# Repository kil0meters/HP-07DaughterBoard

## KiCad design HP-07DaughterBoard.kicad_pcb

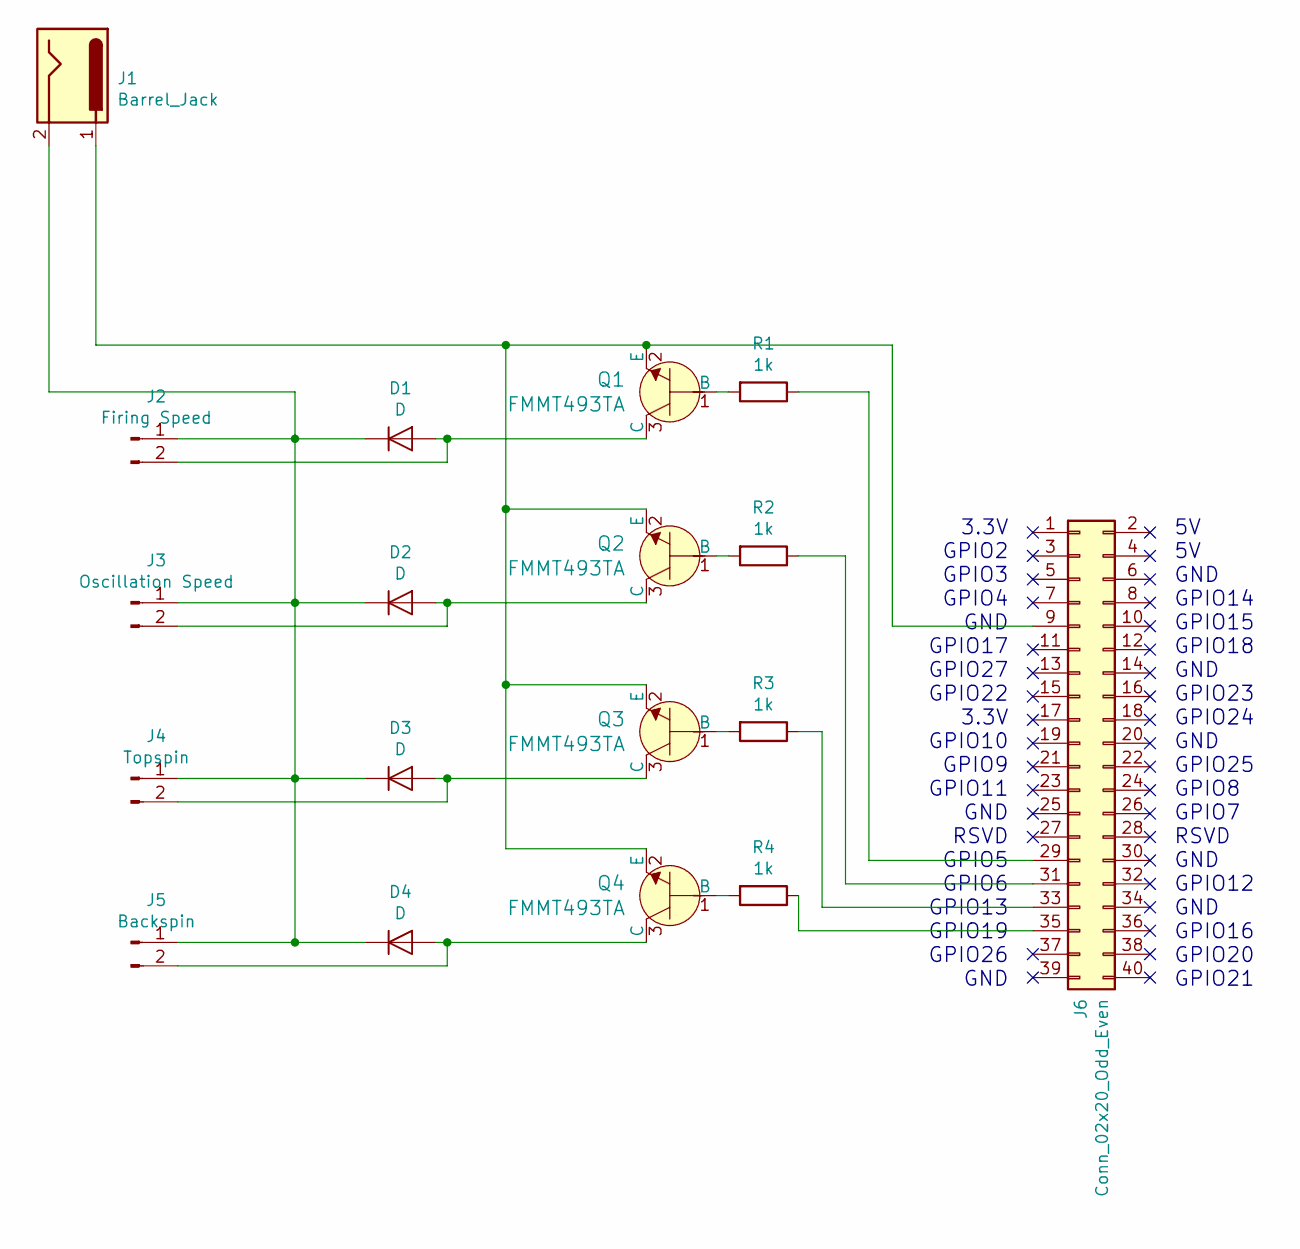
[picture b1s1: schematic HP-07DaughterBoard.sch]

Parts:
D1, D2, D3, D4: D; D_1206_3216Metric_Pad1.42x1.75mm_HandSolder
J1: Barrel_Jack; BarrelJack_CUI_PJ-063AH_Horizontal
J2: Firing Speed; JST_EH_B2B-EH-A_1x02_P2.50mm_Vertical
J3: Oscillation Speed; JST_EH_B2B-EH-A_1x02_P2.50mm_Vertical
J4: Topspin; JST_EH_B2B-EH-A_1x02_P2.50mm_Vertical
J5: Backspin; JST_EH_B2B-EH-A_1x02_P2.50mm_Vertical
J6: Conn_02x20_Odd_Even; PinSocket_2x20_P2.54mm_Vertical
Q1, Q2, Q3, Q4: FMMT493TA; SOT-23-3; MPN FMMT493TA; Digi-Key_PN FMMT493CT-ND
R1, R2, R3, R4: 1k; R_1206_3216Metric_Pad1.42x1.75mm_HandSolder

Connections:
unnamed: D1.1 (K), D2.1 (K), D3.1 (K), D4.1 (K), J1.2, J2.1, J3.1, J4.1, J5.1
unnamed: D1.2 (A), J2.2, Q1.3 (C)
unnamed: D2.2 (A), J3.2, Q2.3 (C)
unnamed: D3.2 (A), J4.2, Q3.3 (C)
unnamed: D4.2 (A), J5.2, Q4.3 (C)
unnamed: J1.1, J6.9, Q1.2 (E), Q2.2 (E), Q3.2 (E), Q4.2 (E)
unnamed: J6.29, R1.1
unnamed: J6.31, R2.1
unnamed: J6.33, R3.1
unnamed: J6.35, R4.1
unnamed: Q1.1 (B), R1.2
unnamed: Q2.1 (B), R2.2
unnamed: Q3.1 (B), R3.2
unnamed: Q4.1 (B), R4.2

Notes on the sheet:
3.3V GPIO2 GPIO3 GPIO4 GND GPIO17 GPIO27 GPIO22 3.3V GPIO10 GPIO9 GPIO11 GND RSVD GPIO5 GPIO6 GPIO13 GPIO19 GPIO26 GND
5V 5V GND GPIO14 GPIO15 GPIO18 GND GPIO23 GPIO24 GND GPIO25 GPIO8 GPIO7 RSVD GND GPIO12 GND GPIO16 GPIO20 GPIO21

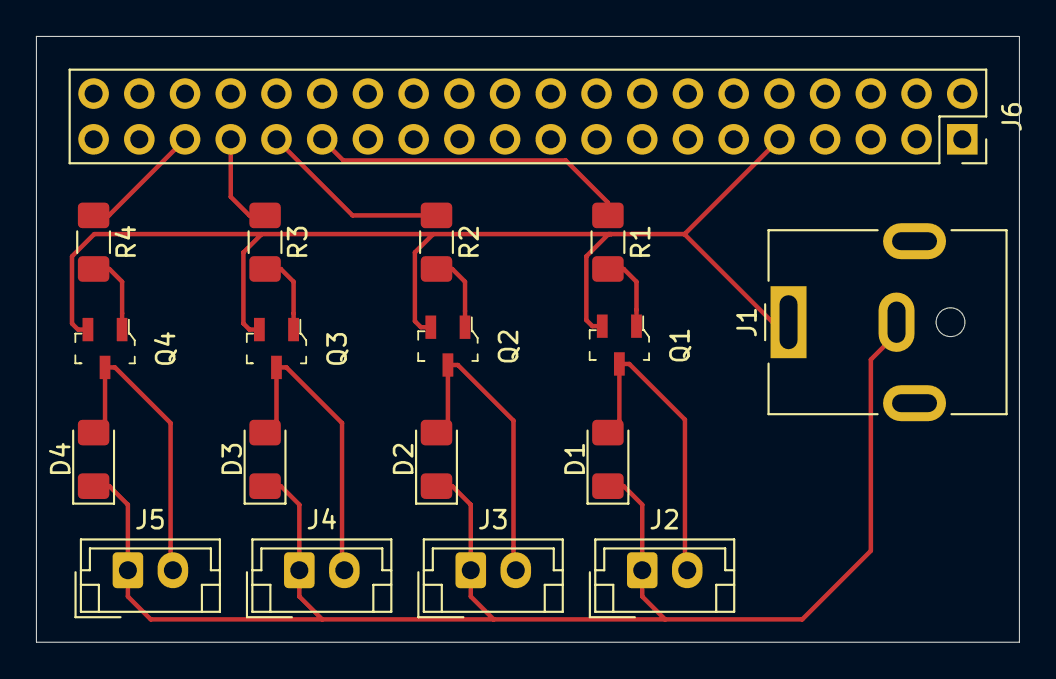
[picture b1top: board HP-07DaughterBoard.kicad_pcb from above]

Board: 2 copper layers, 54.6 x 33.7 mm, 18 parts (0 on the bottom side), 14 nets.

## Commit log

2020-01-10 Initial crappy PCB (kind of)
